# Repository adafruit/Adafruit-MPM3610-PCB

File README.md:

## Adafruit MPM3610 3.3V Buck Converter Breakout PCB

<a href="http://www.adafruit.com/products/4683"><br/>
Click here to purchase one from the Adafruit shop</a>

PCB files for the Adafruit MPM3610 3.3V Buck Converter Breakout.

Format is EagleCAD schematic and board layout
* https://www.adafruit.com/product/4683

### Description

Adafruit MPM3610 3.3V Buck Converter Breakout.

### License

Adafruit invests time and resources providing this open source design, please support Adafruit and open-source hardware by purchasing products from [Adafruit](https://www.adafruit.com)!

Designed by Limor Fried/Ladyada for Adafruit Industries.

Creative Commons Attribution/Share-Alike, all text above must be included in any redistribution.
See license.txt for additional details.

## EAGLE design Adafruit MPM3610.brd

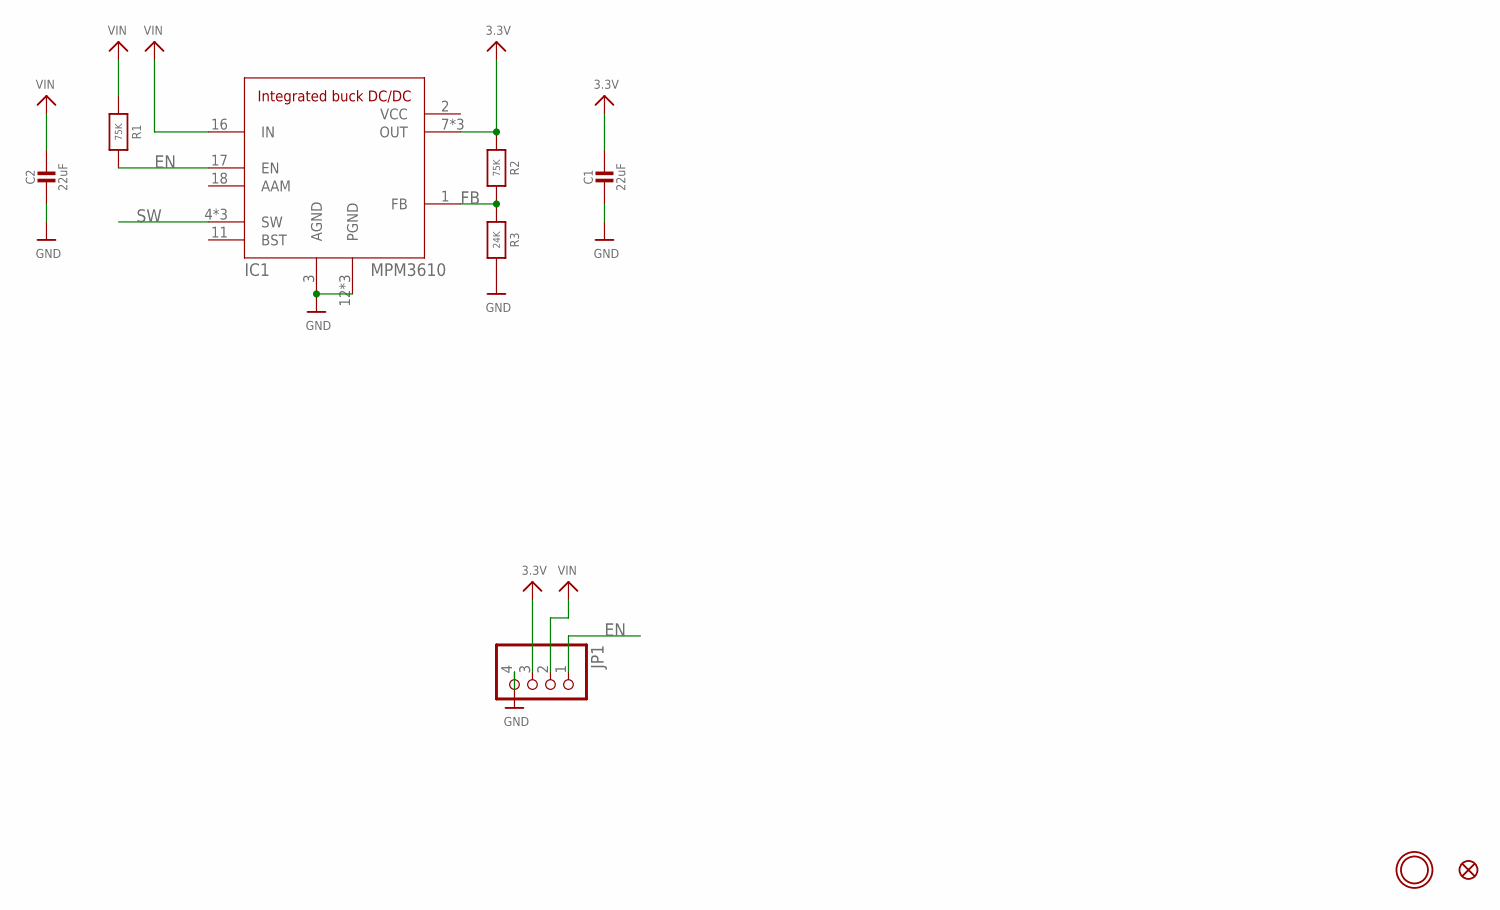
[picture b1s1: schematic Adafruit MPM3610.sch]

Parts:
C1, C2: 22uF; 0805-NO
FID1: FIDUCIAL_1MM
IC1: MPM3610
JP1: HEADER-1X4ROUND; 1X04_ROUND
R1, R2: 75K; 0603-NO
R3: 24K; 0603-NO
U$9: MOUNTINGHOLE2.5; MOUNTINGHOLE_2.5_PLATED

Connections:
3.3V: C1.1, IC1.7 (OUT), IC1.8 (OUT), IC1.9 (OUT), JP1.3, R2.1
EN: IC1.17 (EN), JP1.1, R1.2
FB: IC1.1 (FB), R2.2, R3.1
GND: C1.2, C2.2, IC1.3 (AGND), IC1.12 (PGND), IC1.13 (PGND), IC1.14 (PGND), JP1.4, R3.2
SW: IC1.4 (SW), IC1.5 (SW), IC1.6 (SW)
VCC: IC1.2 (VCC)
VIN: C2.1, IC1.16 (IN), JP1.2, R1.1

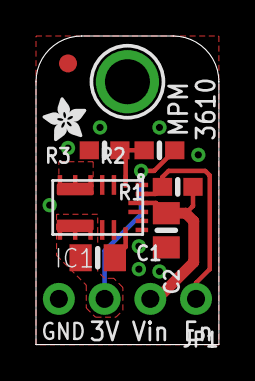
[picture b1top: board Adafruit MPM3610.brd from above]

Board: 2 copper layers, 10.2 x 17.1 mm, 11 parts (1 on the bottom side), 6 nets.

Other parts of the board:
U$10: PCBFEAT-REV-040
U$11: ADAFRUIT_2.5MM

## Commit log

2020-07-24 Uploading board files.

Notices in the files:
parts and their libraries:
microbuilder: This work is placed in the public domain, and may be freely used for commercial and non-commercial work with the following conditions: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
